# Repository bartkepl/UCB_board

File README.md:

# UCB (Universal Control Board)
Control board for testing concepts with SCPI, UART, USB, RS485 and ETHERNET in 3U eurocard format

| Top | Bottom |
|---|---|
|  |  |

---
## Status: ready for prototype order

- Schematic and PCB layout done (4-layer, 56.8 × 100 mm), production files generated.
- Design review completed; DRC/ERC clean (remaining items reviewed and excluded as by-design).
- W5500 clock is sourced from the MCU (MCO1) by default — R80 fitted, R23 (Si5351C CLK0) DNP.
- Firmware: STM32CubeMX skeleton only.

Production outputs: [schematic PDF](prod/sch/UCB_board.pdf) · [PCB PDF](prod/pcb/UCB_board.pdf) · [interactive BOM](prod/ibom/UCB_board_ibom.html) · [gerbers](prod/UCB_board.zip)

---
## Features:
- ARM Cortex-M33 Processor in LQFP100 (STM32H563VIT6) 
- USB 2.0
- 10/100 Ethernet (based on WIZnet W5500)
- UART
- Half-duplex RS485 
- 3U eurocard IEEE 1101.1-1998 format (160x100 mm) — this 56.8 × 100 mm backend board is combined with a 100 × 100 mm front module (e.g. SSM_board)
----

## License and Contribution

[MIT License](/LICENSE)

Open to contributions in both software and hardware!

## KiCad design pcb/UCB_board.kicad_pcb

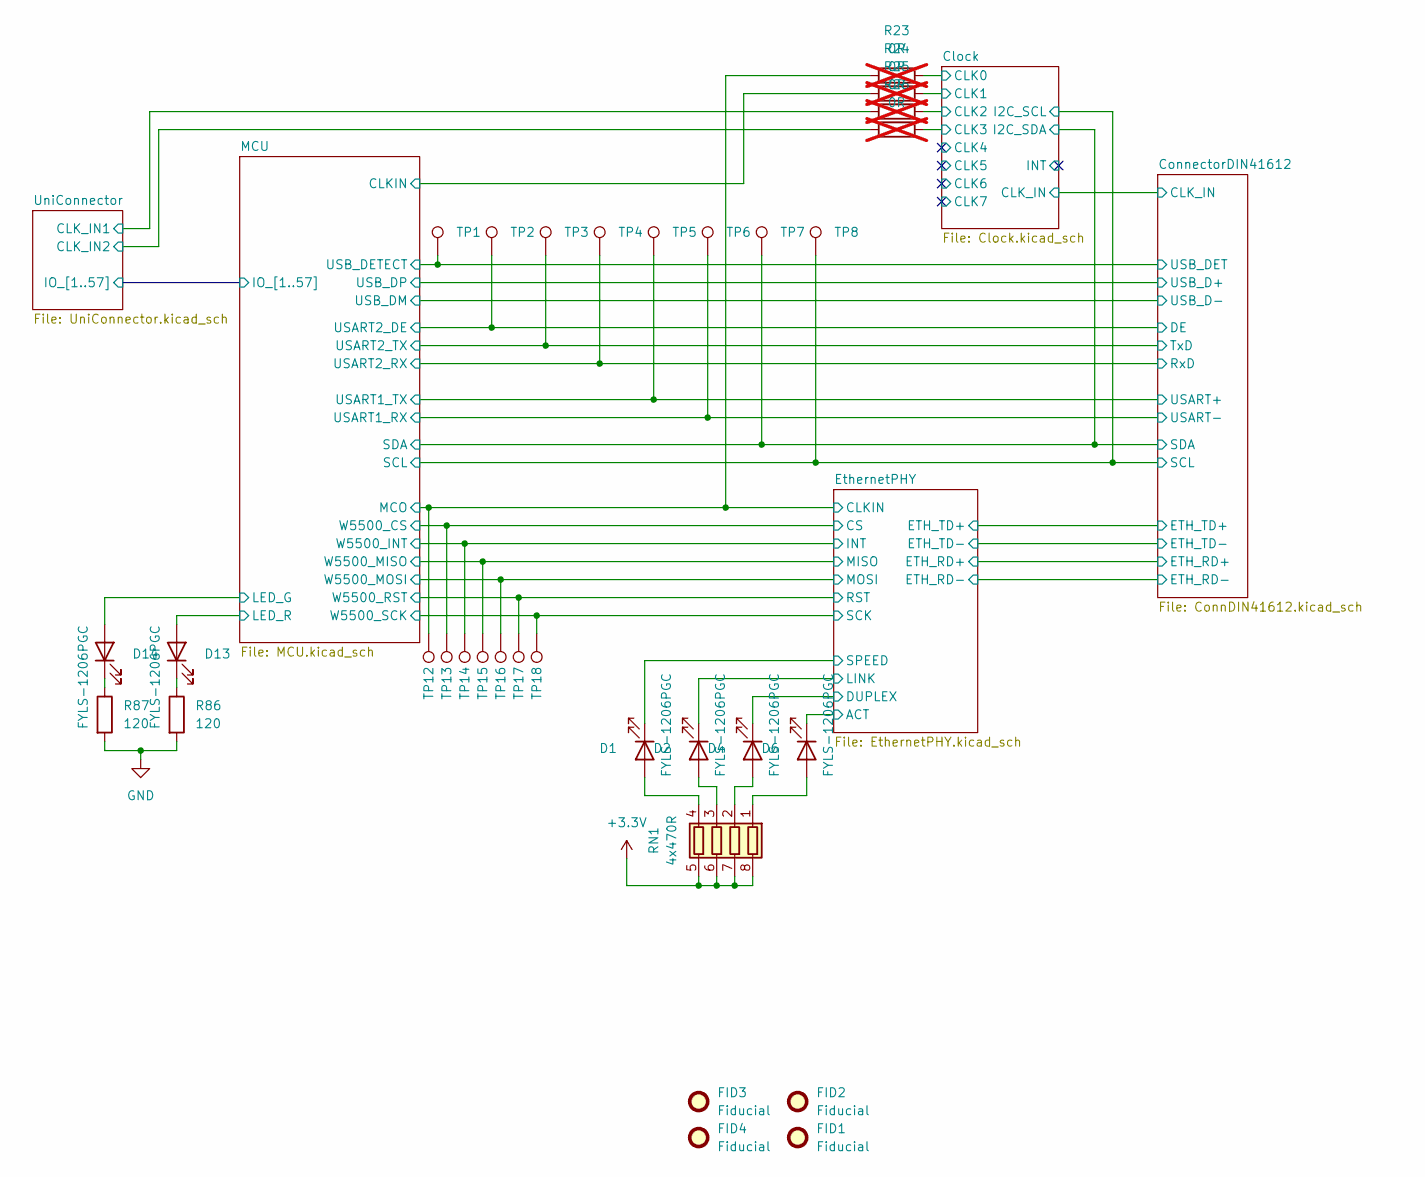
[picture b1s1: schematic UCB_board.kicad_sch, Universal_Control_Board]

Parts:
D1, D2, D4, D6, D13, D14: FYLS-1206PGC; LED_0603_1608Metric; Manufacturer_Part_Number FYLS-1206PGC
FID1, FID2, FID3, FID4: Fiducial; Fiducial_0.5mm_Mask1mm
R23, R24, R25, R26: 0R; R_0402_1005Metric; Manufacturer_Part_Number CRCW04020000Z0TDBC; not fitted
R86, R87: 120; R_0603_1608Metric; Manufacturer_Part_Number 0603SAF1200T5E
RN1: 4x470R; R_Array_Convex_4x0603; Manufacturer_Part_Number 4D03WGJ0471T5E
TP1, TP2, TP3, TP4, TP5, TP6, TP7, TP8, TP12, TP13, TP14, TP15, TP16, TP17, TP18: TestPoint; TestPoint_Pad_D1.0mm

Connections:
+3.3V: RN1.5 (R4.2), RN1.6 (R3.2), RN1.7 (R2.2), RN1.8 (R1.2); also elsewhere on the board
/Clock/CLK0: R23.2; also elsewhere on the board
/Clock/CLK1: R24.2; also elsewhere on the board
/Clock/CLK2: R25.2; also elsewhere on the board
/Clock/CLK3: R26.2; also elsewhere on the board
/ConnectorDIN41612/DE: TP2.1 (1_1); also elsewhere on the board
/ConnectorDIN41612/RxD: TP4.1 (1_1); also elsewhere on the board
/ConnectorDIN41612/TxD: TP3.1 (1_1); also elsewhere on the board
/ConnectorDIN41612/USART+: TP5.1 (1_1); also elsewhere on the board
/ConnectorDIN41612/USART-: TP6.1 (1_1); also elsewhere on the board
/ConnectorDIN41612/USB_DET: TP1.1 (1_1); also elsewhere on the board
/EthernetPHY/ACT: D6.1 (K); also elsewhere on the board
/EthernetPHY/CS: TP13.1 (1_1); also elsewhere on the board
/EthernetPHY/DUPLEX: D4.1 (K); also elsewhere on the board
/EthernetPHY/INT: TP14.1 (1_1); also elsewhere on the board
/EthernetPHY/LINK: D2.1 (K); also elsewhere on the board
/EthernetPHY/MISO: TP15.1 (1_1); also elsewhere on the board
/EthernetPHY/MOSI: TP16.1 (1_1); also elsewhere on the board
/EthernetPHY/RST: TP17.1 (1_1); also elsewhere on the board
/EthernetPHY/SCK: TP18.1 (1_1); also elsewhere on the board
/EthernetPHY/SPEED: D1.1 (K); also elsewhere on the board
/EthernetPHY/XO+: R23.1, TP12.1 (1_1); also elsewhere on the board
/MCU/LED_G: D14.2 (A); also elsewhere on the board
/MCU/LED_R: D13.2 (A); also elsewhere on the board
/MCU/SCL: TP8.1 (1_1); also elsewhere on the board
/MCU/SDA: TP7.1 (1_1); also elsewhere on the board
/MCU/XTAL+: R24.1; also elsewhere on the board
/UniConnector/CLK_IN1: R25.1; also elsewhere on the board
/UniConnector/CLK_IN2: R26.1; also elsewhere on the board
GND: R86.2, R87.2; also elsewhere on the board
unnamed: D1.2 (A), RN1.4 (R4.1)
unnamed: D2.2 (A), RN1.3 (R3.1)
unnamed: D4.2 (A), RN1.2 (R2.1)
unnamed: D6.2 (A), RN1.1 (R1.1)
unnamed: D13.1 (K), R86.1
unnamed: D14.1 (K), R87.1

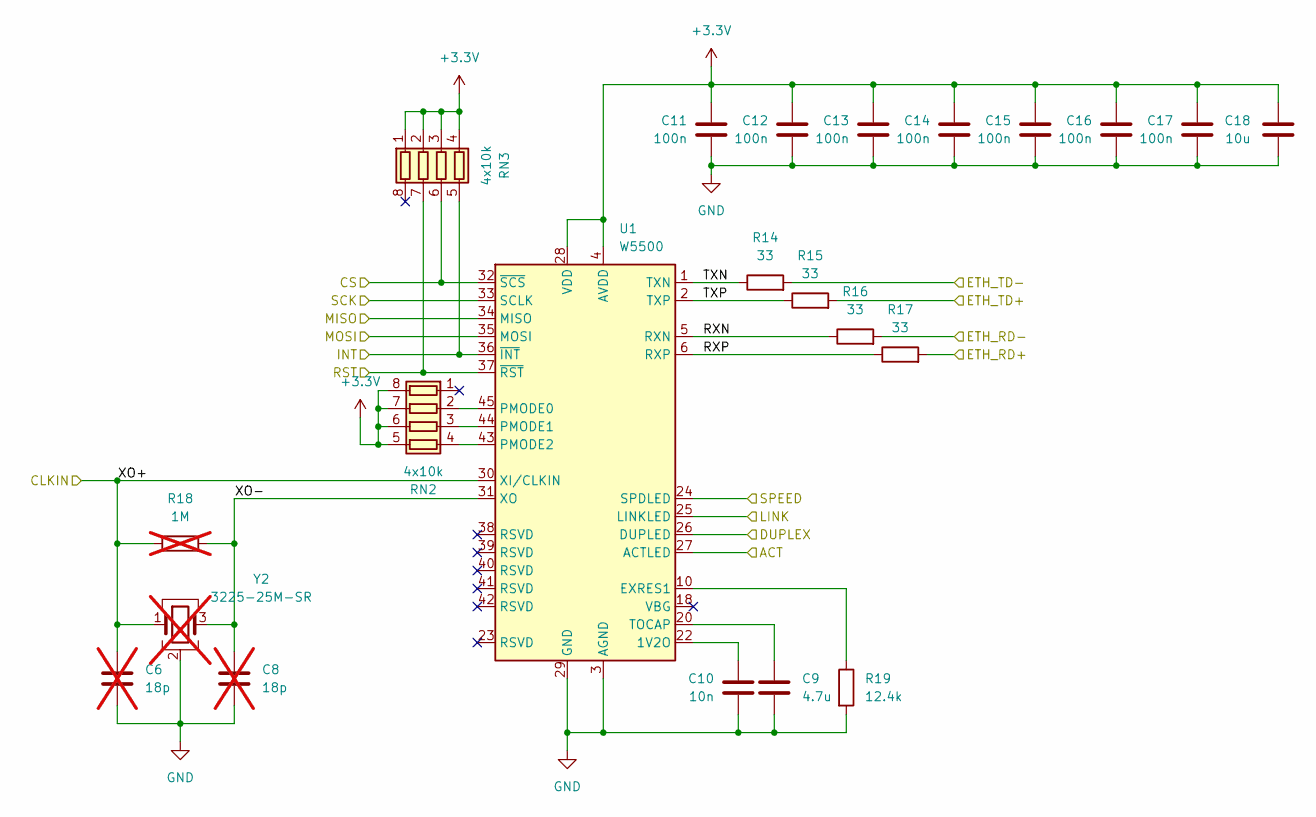
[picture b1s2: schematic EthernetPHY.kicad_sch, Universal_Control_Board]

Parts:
C6, C8: 18p; C_0402_1005Metric_Pad0.74x0.62mm_HandSolder; not fitted
C9: 4.7u; C_0603_1608Metric; Manufacturer_Part_Number 0603X475K100CT
C10: 10n; C_0603_1608Metric; Manufacturer_Part_Number GRM1885C1H103JA01J
C11, C12, C13, C14, C15, C16, C17: 100n; C_0603_1608Metric; Manufacturer_Part_Number GRM188R71H104KA93D
C18: 10u; C_1206_3216Metric; Manufacturer_Part_Number CL31B106KBHNNNE
R14, R15, R16, R17: 33; R_0603_1608Metric; Manufacturer_Part_Number WF06P330JTL
R18: 1M; R_0402_1005Metric_Pad0.72x0.64mm_HandSolder; not fitted
R19: 12.4k; R_0603_1608Metric; Manufacturer_Part_Number ERA3AEB1242V
RN2, RN3: 4x10k; R_Array_Convex_4x0603; Manufacturer_Part_Number 4D03WGJ0103T5E
U1: W5500; LQFP-48_7x7mm_P0.5mm; Manufacturer_Part_Number W5500
Y2: 3225-25M-SR; Crystal_SMD_3225-4Pin_3.2x2.5mm; not fitted

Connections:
+3.3V: C11.2, C12.2, C13.2, C14.2, C15.2, C16.2, C17.2, C18.1, RN2.5 (R4.2), RN2.6 (R3.2), RN2.7 (R2.2), RN2.8 (R1.2), RN3.1 (R1.1), RN3.2 (R2.1), RN3.3 (R3.1), RN3.4 (R4.1), U1.4 (AVDD), U1.8 (AVDD), U1.11 (AVDD), U1.15 (AVDD), U1.17 (AVDD), U1.21 (AVDD), U1.28 (VDD); also elsewhere on the board
/ConnectorDIN41612/ETH_RD+: R17.2; also elsewhere on the board
/ConnectorDIN41612/ETH_RD-: R16.2; also elsewhere on the board
/ConnectorDIN41612/ETH_TD+: R15.2; also elsewhere on the board
/ConnectorDIN41612/ETH_TD-: R14.2; also elsewhere on the board
/EthernetPHY/ACT: U1.27 (ACTLED); also elsewhere on the board
/EthernetPHY/CS: RN3.6 (R3.2), U1.32 (~SCS); also elsewhere on the board
/EthernetPHY/DUPLEX: U1.26 (DUPLED); also elsewhere on the board
/EthernetPHY/INT: RN3.5 (R4.2), U1.36 (~INT); also elsewhere on the board
/EthernetPHY/LINK: U1.25 (LINKLED); also elsewhere on the board
/EthernetPHY/MISO: U1.34 (MISO); also elsewhere on the board
/EthernetPHY/MOSI: U1.35 (MOSI); also elsewhere on the board
/EthernetPHY/RST: RN3.7 (R2.2), U1.37 (~RST); also elsewhere on the board
/EthernetPHY/RXN: R16.1, U1.5 (RXN)
/EthernetPHY/RXP: R17.1, U1.6 (RXP)
/EthernetPHY/SCK: U1.33 (SCLK); also elsewhere on the board
/EthernetPHY/SPEED: U1.24 (SPDLED); also elsewhere on the board
/EthernetPHY/TXN: R14.1, U1.1 (TXN)
/EthernetPHY/TXP: R15.1, U1.2 (TXP)
/EthernetPHY/XO+: C6.1, R18.1, U1.30 (XI/CLKIN), Y2.1; also elsewhere on the board
/EthernetPHY/XO-: C8.1, R18.2, U1.31 (XO), Y2.3
GND: C6.2, C8.2, C9.2, C10.1, C11.1, C12.1, C13.1, C14.1, C15.1, C16.1, C17.1, C18.2, R19.2, U1.3 (AGND), U1.9 (AGND), U1.14 (AGND), U1.16 (AGND), U1.19 (AGND), U1.29 (GND), U1.48 (AGND), Y2.2 (G), Y2.4 (G); also elsewhere on the board
unnamed: RN2.2 (R2.1), U1.45 (PMODE0)
unnamed: RN2.3 (R3.1), U1.44 (PMODE1)
unnamed: RN2.4 (R4.1), U1.43 (PMODE2)
unnamed: C10.2, U1.22 (1V2O)
unnamed: R19.1, U1.10 (EXRES1)
unnamed: C9.1, U1.20 (TOCAP)

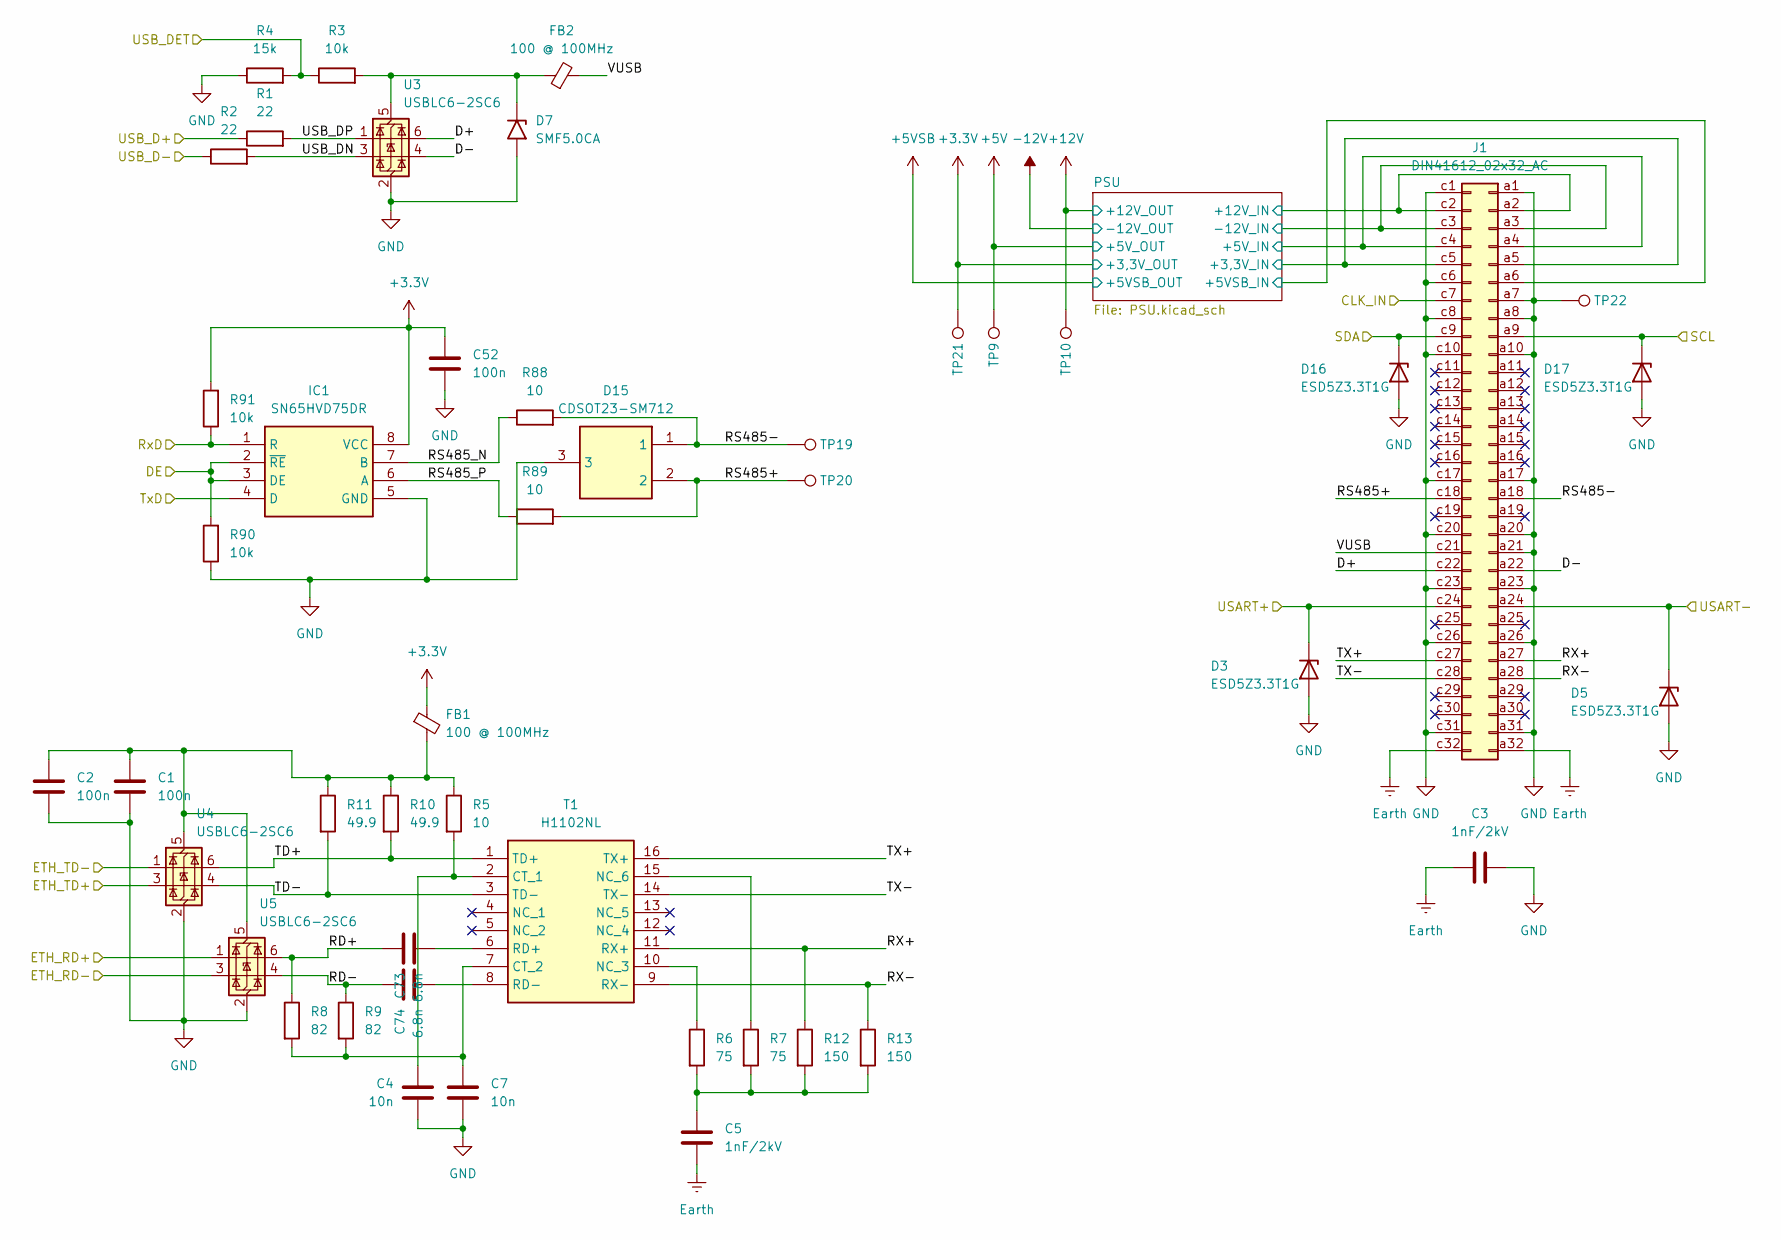
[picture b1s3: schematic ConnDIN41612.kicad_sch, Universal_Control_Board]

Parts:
C1, C2, C52: 100n; C_0603_1608Metric; Manufacturer_Part_Number GRM188R71H104KA93D
C3, C5: 1nF/2kV; C_1206_3216Metric; Manufacturer_Part_Number 1206B102K202
C4, C7: 10n; C_0603_1608Metric; Manufacturer_Part_Number GRM1885C1H103JA01J
C73, C74: 6.8n; C_0603_1608Metric
D3, D5, D16, D17: ESD5Z3.3T1G; D_SOD-523; Manufacturer_Part_Number ESD5Z3.3T1G
D7: SMF5.0CA; D_SMF; Manufacturer_Part_Number SMF5.0CA
D15: CDSOT23-SM712; SOT95P230X117-3N; Manufacturer_Part_Number CDSOT23-SM712
FB1, FB2: 100 @ 100MHz; L_0603_1608Metric; Manufacturer_Part_Number WLBD1608HCU101TL
IC1: SN65HVD75DR; SOIC127P600X175-8N; Manufacturer_Part_Number SN65HVD75DR
J1: DIN41612_02x32_AC; DIN41612_C_2x32_Male_Horizontal_THT
R1, R2: 22; R_0402_1005Metric; Manufacturer_Part_Number 0402WGJ0220TCE
R3, R90, R91: 10k; R_0603_1608Metric; Manufacturer_Part_Number CRCW060310K0FKTABC
R4: 15k; R_0603_1608Metric; Manufacturer_Part_Number RC0603FR-0715KL
R5, R88, R89: 10; R_0603_1608Metric
R6, R7: 75; R_0603_1608Metric; Manufacturer_Part_Number 0603SAJ0750T5E
R8, R9: 82; R_0603_1608Metric; Manufacturer_Part_Number RC0603JR-0782RL
R10, R11: 49.9; R_0603_1608Metric; Manufacturer_Part_Number CRCW060349R9FKTABC
R12, R13: 150; R_0603_1608Metric; Manufacturer_Part_Number 1-2176339-5
T1: H1102NL; SOIC127P940X597-16N; Manufacturer_Part_Number H1102NL
TP9, TP10, TP19, TP20, TP21, TP22: TestPoint; TestPoint_Pad_D1.0mm
U3, U4, U5: USBLC6-2SC6; SOT-23-6_Handsoldering; Manufacturer_Part_Number USBLC6-2SC6

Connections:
+3.3V: C52.1, FB1.1, IC1.8 (VCC), R91.2, TP21.1 (1_1); also elsewhere on the board
+5V: TP9.1 (1_1); also elsewhere on the board
+12V: TP10.1 (1_1); also elsewhere on the board
/Clock/CLK_IN: J1.c7; also elsewhere on the board
/ConnectorDIN41612/D+: J1.c22, U3.6 (I/O1)
/ConnectorDIN41612/D-: J1.a22, U3.4 (I/O2)
/ConnectorDIN41612/DE: IC1.2 (~RE), IC1.3 (DE), R90.2; also elsewhere on the board
/ConnectorDIN41612/ETH_RD+: U5.1 (I/O1); also elsewhere on the board
/ConnectorDIN41612/ETH_RD-: U5.3 (I/O2); also elsewhere on the board
/ConnectorDIN41612/ETH_TD+: U4.3 (I/O2); also elsewhere on the board
/ConnectorDIN41612/ETH_TD-: U4.1 (I/O1); also elsewhere on the board
/ConnectorDIN41612/PSU/+3,3V_IN: J1.a5, J1.c5; also elsewhere on the board
/ConnectorDIN41612/PSU/+5VSB_IN: J1.a6
/ConnectorDIN41612/PSU/+5V_IN: J1.a4, J1.c4; also elsewhere on the board
/ConnectorDIN41612/PSU/+12V_IN: J1.a2, J1.c2; also elsewhere on the board
/ConnectorDIN41612/PSU/-12V_IN: J1.a3, J1.c3; also elsewhere on the board
/ConnectorDIN41612/RD+: C73.2, R8.1, U5.6 (I/O1)
/ConnectorDIN41612/RD-: C74.2, R9.1, U5.4 (I/O2)
/ConnectorDIN41612/RS485+: D15.2, J1.c18, R89.2, TP20.1 (1_1)
/ConnectorDIN41612/RS485-: D15.1, J1.a18, R88.2, TP19.1 (1_1)
/ConnectorDIN41612/RS485_N: IC1.7 (B), R88.1
/ConnectorDIN41612/RS485_P: IC1.6 (A), R89.1
/ConnectorDIN41612/RX+: J1.a27, R12.1, T1.11 (RX+)
/ConnectorDIN41612/RX-: J1.a28, R13.1, T1.9 (RX-)
/ConnectorDIN41612/RxD: IC1.1 (R), R91.1; also elsewhere on the board
/ConnectorDIN41612/TD+: R10.2, T1.1 (TD+), U4.6 (I/O1)
/ConnectorDIN41612/TD-: R11.2, T1.3 (TD-), U4.4 (I/O2)
/ConnectorDIN41612/TX+: J1.c27, T1.16 (TX+)
/ConnectorDIN41612/TX-: J1.c28, T1.14 (TX-)
/ConnectorDIN41612/TxD: IC1.4 (D); also elsewhere on the board
/ConnectorDIN41612/USART+: D3.1 (K), J1.c24; also elsewhere on the board
/ConnectorDIN41612/USART-: D5.1 (K), J1.a24; also elsewhere on the board
/ConnectorDIN41612/USB_D+: R1.1; also elsewhere on the board
/ConnectorDIN41612/USB_D-: R2.1; also elsewhere on the board
/ConnectorDIN41612/USB_DET: R3.1, R4.2; also elsewhere on the board
/ConnectorDIN41612/USB_DN: R2.2, U3.3 (I/O2)
/ConnectorDIN41612/USB_DP: R1.2, U3.1 (I/O1)
/ConnectorDIN41612/VUSB: FB2.2, J1.c21
/MCU/SCL: D17.1 (K), J1.a9; also elsewhere on the board
/MCU/SDA: D16.1 (K), J1.c9; also elsewhere on the board
Earth: C3.1, C5.2, J1.a32, J1.c32; also elsewhere on the board
GND: C1.2, C2.2, C3.2, C4.1, C7.2, C52.2, D3.2 (A), D5.2 (A), D7.2 (A2), D15.3, D16.2 (A), D17.2 (A), IC1.5 (GND), J1.a1, J1.a7, J1.a8, J1.a10, J1.a17, J1.a20, J1.a21, J1.a23, J1.a26, J1.a31, J1.c1, J1.c6, J1.c8, J1.c10, J1.c17, J1.c20, J1.c23, J1.c26, J1.c31, R4.1, R90.1, TP22.1 (1_1), U3.2 (GND), U4.2 (GND), U5.2 (GND); also elsewhere on the board
unnamed: C5.1, R6.2, R7.2, R12.2, R13.2
unnamed: D7.1 (A1), FB2.1, R3.2, U3.5 (VBUS)
unnamed: C4.2, R5.2, T1.2 (CT_1)
unnamed: C7.1, R8.2, R9.2, T1.7 (CT_2)
unnamed: R6.1, T1.10 (NC_3)
unnamed: R7.1, T1.15 (NC_6)
unnamed: C73.1, T1.6 (RD+)
unnamed: C74.1, T1.8 (RD-)
unnamed: C1.1, C2.1, FB1.2, R5.1, R10.1, R11.1, U4.5 (VBUS), U5.5 (VBUS)

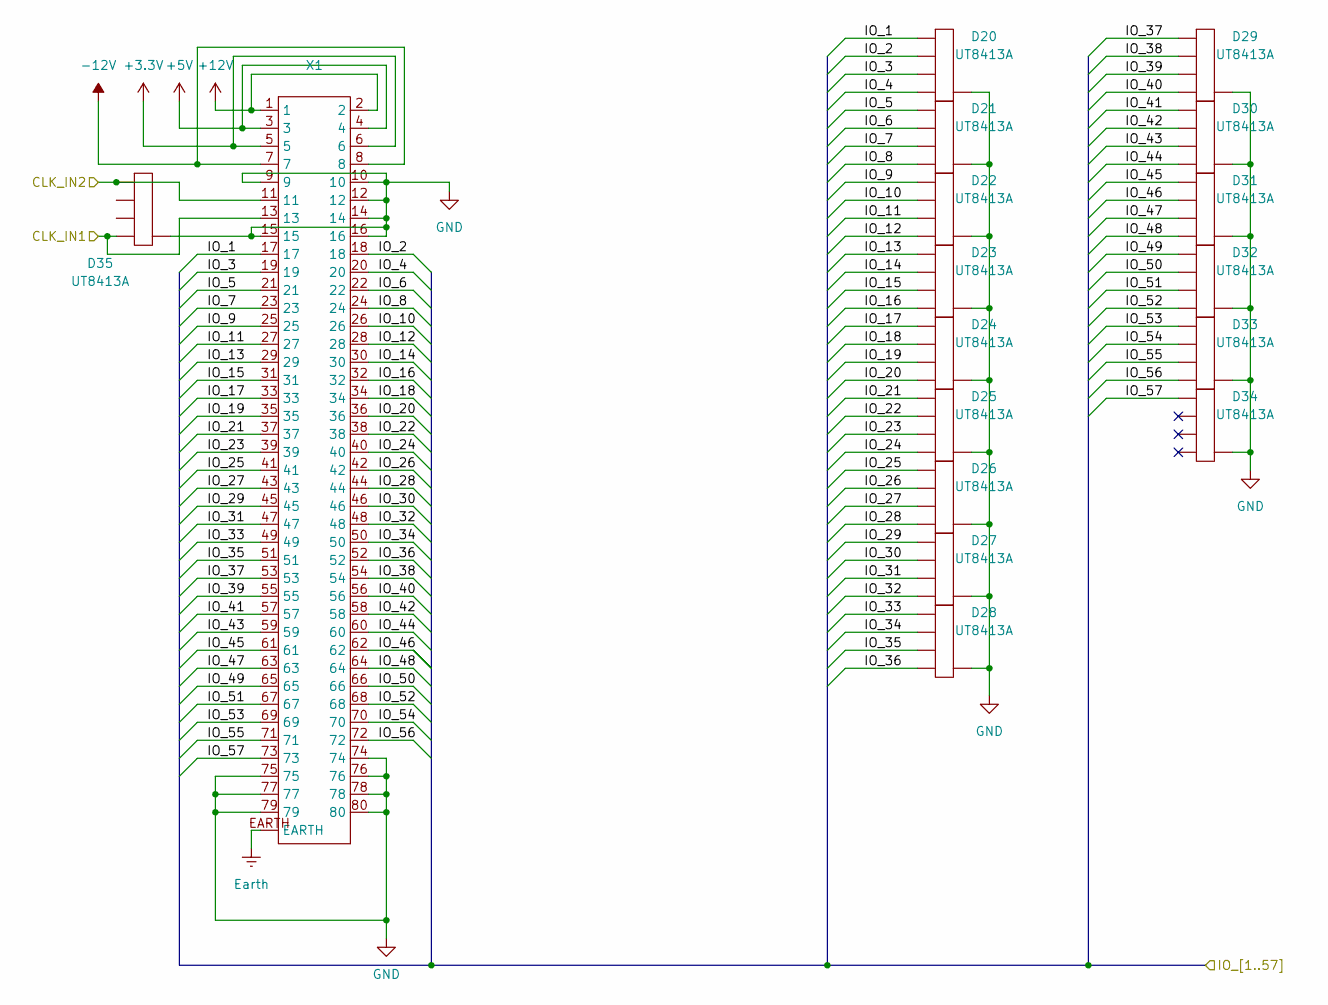
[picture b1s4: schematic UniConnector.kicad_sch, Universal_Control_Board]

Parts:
D20, D21, D22, D23, D24, D25, D26, D27, D28, D29, D30, D31, D32, D33, D34, D35: UT8413A; Diodes_UDFN-10_1.0x2.5mm_P0.5mm; Manufacturer_Part_Number UT8413A
X1: UniConnector

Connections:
+3.3V: X1.5, X1.6; also elsewhere on the board
+5V: X1.3, X1.4; also elsewhere on the board
+12V: X1.1, X1.2; also elsewhere on the board
-12V: X1.7, X1.8; also elsewhere on the board
/MCU/IO_1: D20.5, D20.6, X1.17; also elsewhere on the board
/MCU/IO_2: D20.4, D20.7, X1.18; also elsewhere on the board
/MCU/IO_3: D20.2, D20.9, X1.19; also elsewhere on the board
/MCU/IO_4: D20.1, D20.10, X1.20; also elsewhere on the board
/MCU/IO_5: D21.5, D21.6, X1.21; also elsewhere on the board
/MCU/IO_6: D21.4, D21.7, X1.22; also elsewhere on the board
/MCU/IO_7: D21.2, D21.9, X1.23; also elsewhere on the board
/MCU/IO_8: D21.1, D21.10, X1.24; also elsewhere on the board
/MCU/IO_9: D22.5, D22.6, X1.25; also elsewhere on the board
/MCU/IO_10: D22.4, D22.7, X1.26; also elsewhere on the board
/MCU/IO_11: D22.2, D22.9, X1.27; also elsewhere on the board
/MCU/IO_12: D22.1, D22.10, X1.28; also elsewhere on the board
/MCU/IO_13: D23.5, D23.6, X1.29; also elsewhere on the board
/MCU/IO_14: D23.4, D23.7, X1.30; also elsewhere on the board
/MCU/IO_15: D23.2, D23.9, X1.31; also elsewhere on the board
/MCU/IO_16: D23.1, D23.10, X1.32; also elsewhere on the board
/MCU/IO_17: D24.5, D24.6, X1.33; also elsewhere on the board
/MCU/IO_18: D24.4, D24.7, X1.34; also elsewhere on the board
/MCU/IO_19: D24.2, D24.9, X1.35; also elsewhere on the board
/MCU/IO_20: D24.1, D24.10, X1.36; also elsewhere on the board
/MCU/IO_21: D25.5, D25.6, X1.37; also elsewhere on the board
/MCU/IO_22: D25.4, D25.7, X1.38; also elsewhere on the board
/MCU/IO_23: D25.2, D25.9, X1.39; also elsewhere on the board
/MCU/IO_24: D25.1, D25.10, X1.40; also elsewhere on the board
/MCU/IO_25: D26.5, D26.6, X1.41; also elsewhere on the board
/MCU/IO_26: D26.4, D26.7, X1.42; also elsewhere on the board
/MCU/IO_27: D26.2, D26.9, X1.43; also elsewhere on the board
/MCU/IO_28: D26.1, D26.10, X1.44; also elsewhere on the board
/MCU/IO_29: D27.5, D27.6, X1.45; also elsewhere on the board
/MCU/IO_30: D27.4, D27.7, X1.46; also elsewhere on the board
/MCU/IO_31: D27.2, D27.9, X1.47; also elsewhere on the board
/MCU/IO_32: D27.1, D27.10, X1.48; also elsewhere on the board
/MCU/IO_33: D28.5, D28.6, X1.49; also elsewhere on the board
/MCU/IO_34: D28.4, D28.7, X1.50; also elsewhere on the board
/MCU/IO_35: D28.2, D28.9, X1.51; also elsewhere on the board
/MCU/IO_36: D28.1, D28.10, X1.52; also elsewhere on the board
/MCU/IO_37: D29.5, D29.6, X1.53; also elsewhere on the board
/MCU/IO_38: D29.4, D29.7, X1.54; also elsewhere on the board
/MCU/IO_39: D29.2, D29.9, X1.55; also elsewhere on the board
/MCU/IO_40: D29.1, D29.10, X1.56; also elsewhere on the board
/MCU/IO_41: D30.5, D30.6, X1.57; also elsewhere on the board
/MCU/IO_42: D30.4, D30.7, X1.58; also elsewhere on the board
/MCU/IO_43: D30.2, D30.9, X1.59; also elsewhere on the board
/MCU/IO_44: D30.1, D30.10, X1.60; also elsewhere on the board
/MCU/IO_45: D31.5, D31.6, X1.61; also elsewhere on the board
/MCU/IO_46: D31.4, D31.7, X1.62; also elsewhere on the board
/MCU/IO_47: D31.2, D31.9, X1.63; also elsewhere on the board
/MCU/IO_48: D31.1, D31.10, X1.64; also elsewhere on the board
/MCU/IO_49: D32.5, D32.6, X1.65; also elsewhere on the board
/MCU/IO_50: D32.4, D32.7, X1.66; also elsewhere on the board
/MCU/IO_51: D32.2, D32.9, X1.67; also elsewhere on the board
/MCU/IO_52: D32.1, D32.10, X1.68; also elsewhere on the board
/MCU/IO_53: D33.5, D33.6, X1.69; also elsewhere on the board
/MCU/IO_54: D33.4, D33.7, X1.70; also elsewhere on the board
/MCU/IO_55: D33.2, D33.9, X1.71; also elsewhere on the board
/MCU/IO_56: D33.1, D33.10, X1.72; also elsewhere on the board
/MCU/IO_57: D34.5, D34.6, X1.73; also elsewhere on the board
/UniConnector/CLK_IN1: D35.1, D35.10, X1.13; also elsewhere on the board
/UniConnector/CLK_IN2: D35.5, D35.6, X1.11; also elsewhere on the board
Earth: X1.EARTH; also elsewhere on the board
GND: D20.3, D20.8, D21.3, D21.8, D22.3, D22.8, D23.3, D23.8, D24.3, D24.8, D25.3, D25.8, D26.3, D26.8, D27.3, D27.8, D28.3, D28.8, D29.3, D29.8, D30.3, D30.8, D31.3, D31.8, D32.3, D32.8, D33.3, D33.8, D34.3, D34.8, D35.3, D35.8, X1.9, X1.10, X1.12, X1.14, X1.15, X1.16, X1.74, X1.75, X1.76, X1.77, X1.78, X1.79, X1.80; also elsewhere on the board
unnamed: D35.2, D35.9
unnamed: D35.4, D35.7

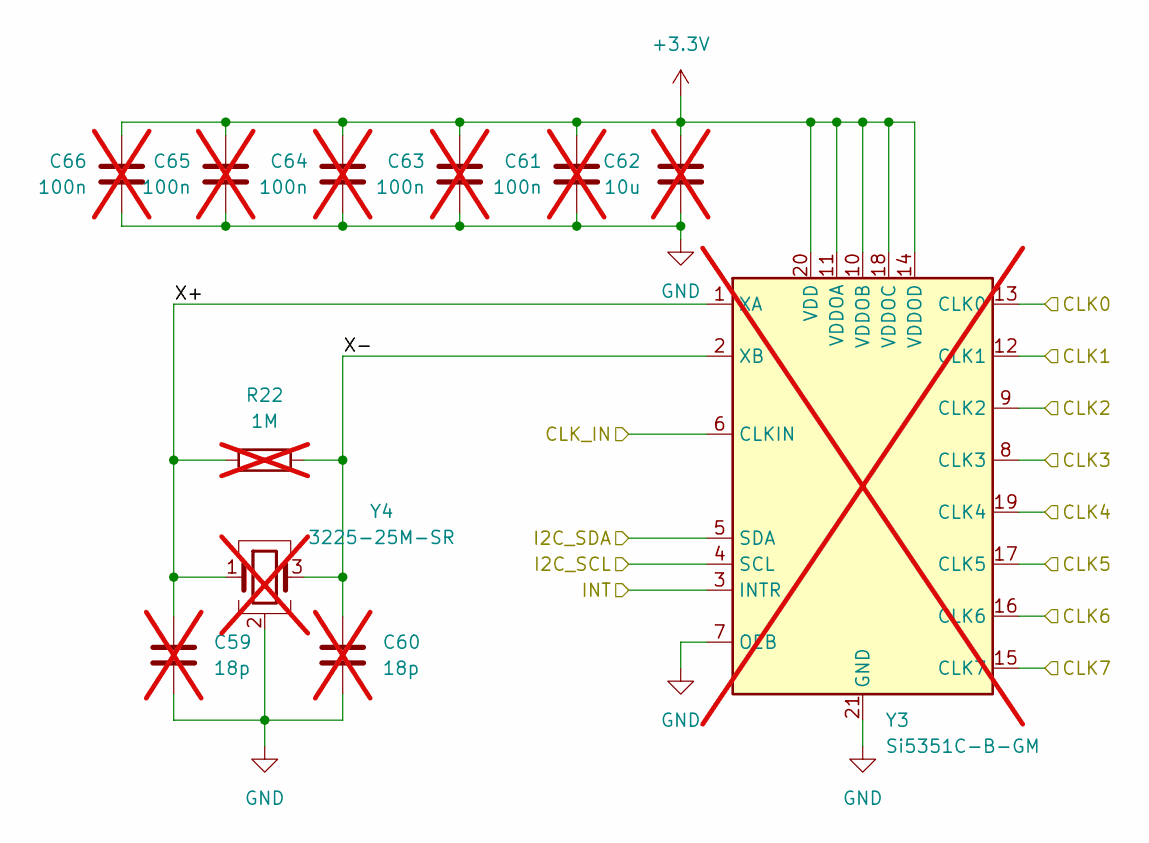
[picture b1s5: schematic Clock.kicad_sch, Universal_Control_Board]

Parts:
C59, C60: 18p; C_0402_1005Metric; not fitted
C61, C63, C64, C65, C66: 100n; C_0603_1608Metric; Manufacturer_Part_Number GRM188R71H104KA93D; not fitted
C62: 10u; C_1206_3216Metric; Manufacturer_Part_Number CL31B106KBHNNNE; not fitted
R22: 1M; R_0603_1608Metric; Manufacturer_Part_Number 0603SAF1004T5E; not fitted
Y3: Si5351C-B-GM; QFN-20-1EP_4x4mm_P0.5mm_EP2.5x2.5mm; Manufacturer_Part_Number Si5351C-B-GM; not fitted
Y4: 3225-25M-SR; Crystal_SMD_3225-4Pin_3.2x2.5mm; Manufacturer_Part_Number 3225-25M-SR; not fitted

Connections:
+3.3V: C61.2, C62.1, C63.2, C64.2, C65.2, C66.2, Y3.10 (VDDOB), Y3.11 (VDDOA), Y3.14 (VDDOD), Y3.18 (VDDOC), Y3.20 (VDD); also elsewhere on the board
/Clock/CLK0: Y3.13 (CLK0); also elsewhere on the board
/Clock/CLK1: Y3.12 (CLK1); also elsewhere on the board
/Clock/CLK2: Y3.9 (CLK2); also elsewhere on the board
/Clock/CLK3: Y3.8 (CLK3); also elsewhere on the board
/Clock/CLK4: Y3.19 (CLK4)
/Clock/CLK5: Y3.17 (CLK5)
/Clock/CLK6: Y3.16 (CLK6)
/Clock/CLK7: Y3.15 (CLK7)
/Clock/CLK_IN: Y3.6 (CLKIN); also elsewhere on the board
/Clock/INT: Y3.3 (INTR)
/Clock/X+: C59.1, R22.1, Y3.1 (XA), Y4.1
/Clock/X-: C60.1, R22.2, Y3.2 (XB), Y4.3
/MCU/SCL: Y3.4 (SCL); also elsewhere on the board
/MCU/SDA: Y3.5 (SDA); also elsewhere on the board
GND: C59.2, C60.2, C61.1, C62.2, C63.1, C64.1, C65.1, C66.1, Y3.7 (OEB), Y3.21 (GND), Y4.2 (G), Y4.4 (G); also elsewhere on the board
